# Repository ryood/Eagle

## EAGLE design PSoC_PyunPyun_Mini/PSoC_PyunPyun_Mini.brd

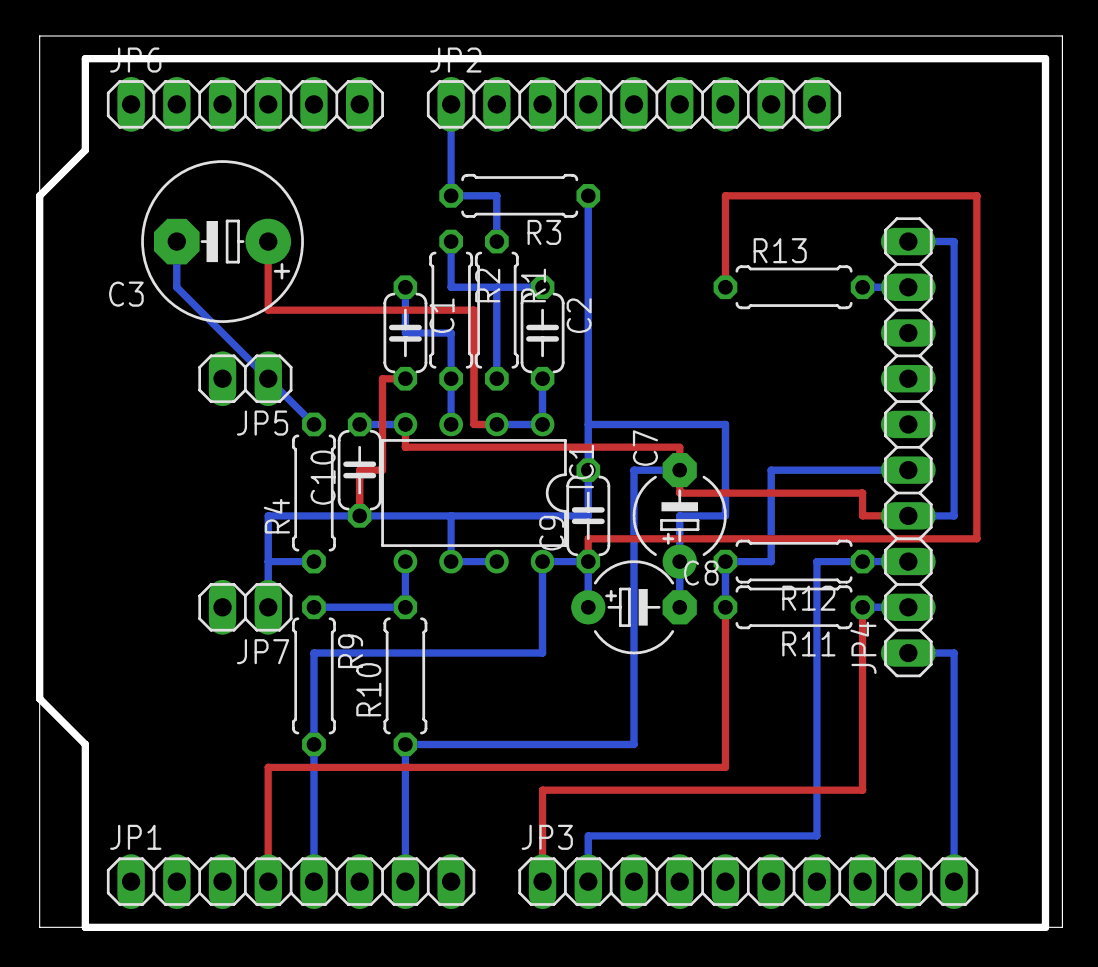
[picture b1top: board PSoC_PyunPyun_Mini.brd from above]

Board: 2 copper layers, 56.8 x 49.5 mm, 24 parts (0 on the bottom side), 14 nets.

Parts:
C1, C2: 0.001uF; C050-024X044
C3: 220uF; E5-8,5
C7, C8: 47uF; E5-5
C9, C10: 0.1uF; C050-024X044
IC1: LM358N; DIL08
JP1: 1X08
JP2: 1X09
JP3: 1X10
JP4: I2C-LCD; 1X10
JP5: RCA_HOT; 1X02
JP6: 1X06
JP7: RCA_GND; 1X02
R1, R2, R4, R9, R10: 10k; 0207/7
R3: 2.2k; 0207/7
R11, R12: 3.3k; 0207/7
R13: 330; 0207/7

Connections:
+3.3V: JP1.4, JP4.5, R11.2, R12.2
+5V: C8.+, C9.1, IC1.8, JP1.5, R9.2, R13.1
AGND: C1.2, C7.+, C8.-, C9.2, C10.1, IC1.6, IC1.7, JP7.1, R3.1, R4.1
GND: C7.-, C10.2, IC1.4, JP1.7, JP4.4, JP4.10, R10.1
IDAC8: JP2.1, R1.1, R3.2
unnamed: C2.1, R1.2, R2.1
unnamed: C1.1, IC1.3, R2.2
unnamed: C2.2, C3.+, IC1.1, IC1.2
unnamed: JP4.9, R13.2
unnamed: C3.-, JP5.1, R4.2
unnamed: IC1.5, R9.1, R10.2
RST: JP3.10, JP4.1
SCL: JP3.1, JP4.2, R11.1
SDA: JP3.2, JP4.3, R12.1
